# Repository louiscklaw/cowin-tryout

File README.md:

# COWIN_TRYOUT

DHT22  (Temperature and Humidity)
BMP280 (pressure sensor)
DS1307 (RTC)

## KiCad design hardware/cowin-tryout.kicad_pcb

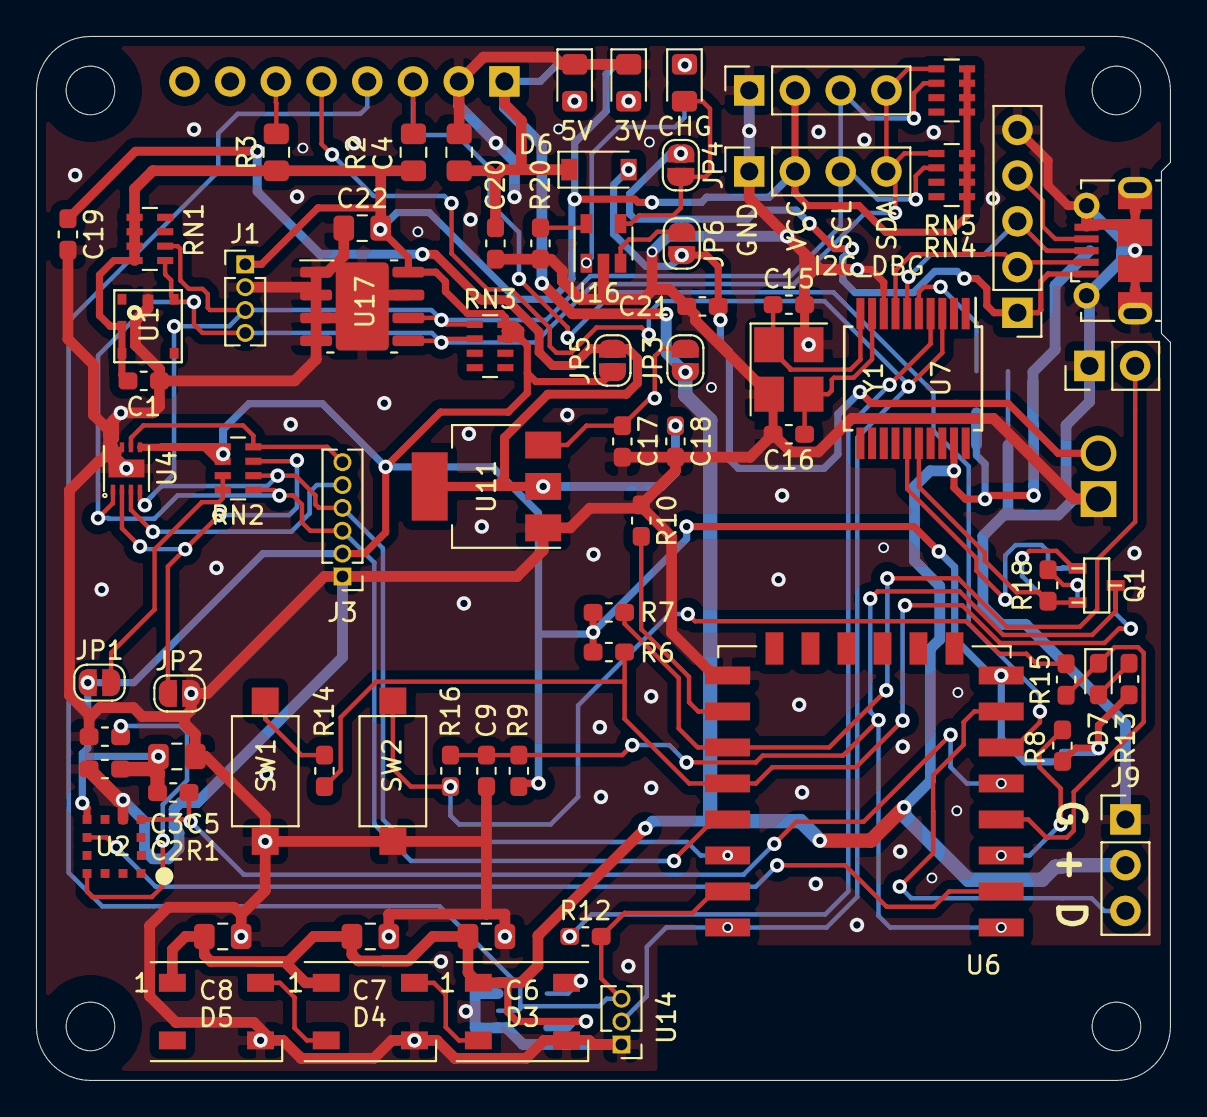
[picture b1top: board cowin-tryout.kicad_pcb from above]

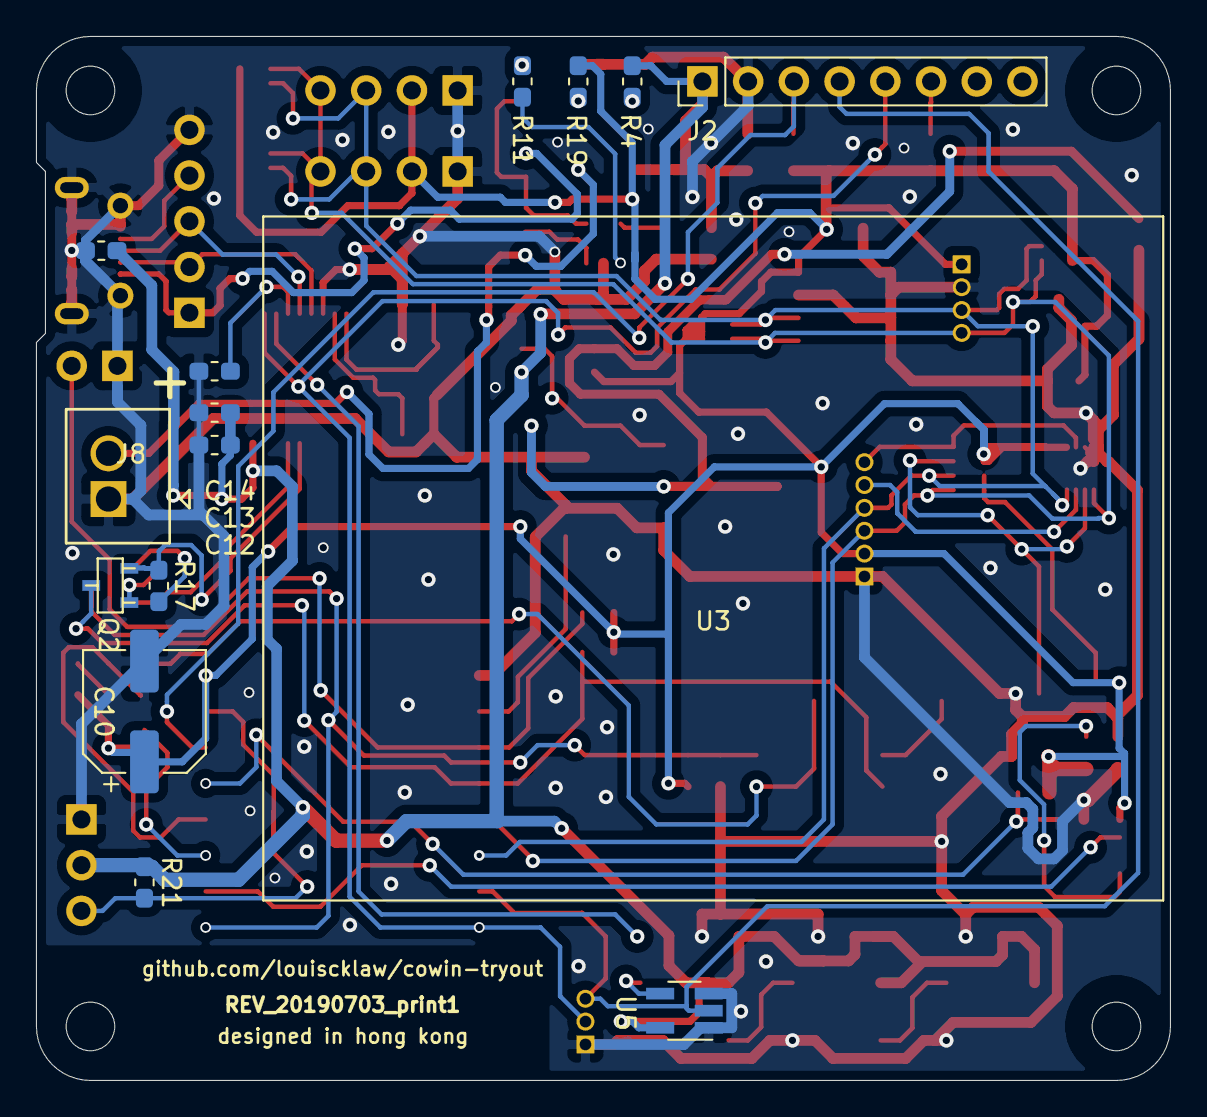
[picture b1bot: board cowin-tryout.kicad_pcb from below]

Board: 2 copper layers, 63.0 x 58.0 mm, 94 parts (15 on the bottom side), 51 nets.

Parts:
C1, C2, C9, C13, C17, C18: C104,0603; C_0603_1608Metric_Pad1.05x0.95mm_HandSolder
C3: C102,0603; C_0603_1608Metric_Pad1.05x0.95mm_HandSolder
C4: C106; C_0805_2012Metric_Pad1.15x1.40mm_HandSolder
C5: C104,0805; C_0805_2012Metric_Pad1.15x1.40mm_HandSolder
C6, C7, C8, C22: C106,0805; C_0805_2012Metric_Pad1.15x1.40mm_HandSolder
C10: CP100uf,10V; CP_Elec_6.3x5.3
C11: C475,0603; C_0603_1608Metric_Pad1.05x0.95mm_HandSolder
C12: C225,0603; C_0603_1608Metric_Pad1.05x0.95mm_HandSolder
C14: C103,0603; C_0603_1608Metric_Pad1.05x0.95mm_HandSolder
C15, C16: C22pf,0603; C_0603_1608Metric_Pad1.05x0.95mm_HandSolder
C19, C20, C21: C106,0603; C_0603_1608Metric_Pad1.05x0.95mm_HandSolder
D1: 5V; LED_0805_2012Metric_Pad1.15x1.40mm_HandSolder
D3, D4, D5: WS2812B; LED_WS2812B_5050_white
D6: D_1N4148_T4; D_SOD-123
D7: LED_BLUE,0603; LED_0603_1608Metric_Pad1.05x0.95mm_HandSolder
D8: 3V; LED_0805_2012Metric_Pad1.15x1.40mm_HandSolder
D9: CHG; LED_0805_2012Metric_Pad1.15x1.40mm_HandSolder
H1, H2, H3, H4: MOUNT_M2.5; MountingHole_2.7mm_M2.5,rpi_like
J1: BMP180_HEADER; PinHeader_1x04_P1.27mm_Vertical
J2: CONN_PMS; PinHeader_1x08_P2.54mm_Vertical
J3: SHT3x_HEADER; PinHeader_1x06_P1.27mm_Vertical
J7: DEBUG_HEADER; PinHeader_1x02_P2.54mm_Vertical
J8: BAT; JST_B2B-XH-A-2.54
J9: DHT22_HEADER; PinHeader_1x03_P2.54mm_Vertical
J10: USB_DBG; PinHeader_1x05_P2.54mm_Vertical
JP1: SolderJumper_2_Open_round; SolderJumper-2_P1.3mm_Open_RoundedPad1.0x1.5mm
JP2: J_ADDR; SolderJumper-2_P1.3mm_Open_RoundedPad1.0x1.5mm
JP3, JP4: 5V_EN; SolderJumper-2_P1.3mm_Open_RoundedPad1.0x1.5mm
JP5: 3V_EN; SolderJumper-2_P1.3mm_Open_RoundedPad1.0x1.5mm
JP6: OUT_EN; SolderJumper-2_P1.3mm_Open_RoundedPad1.0x1.5mm
Q1, Q2: SS9013_J3; 9013,J3,SOT23
R1, R20, R21: R103,0603; R_0603_1608Metric_Pad1.05x0.95mm_HandSolder
R2, R3: R103; R_0805_2012Metric_Pad1.15x1.40mm_HandSolder
R4: R102; R_0603_1608Metric_Pad1.05x0.95mm_HandSolder
R6, R7, R8, R9, R10, R17, R18: R123,0603; R_0603_1608Metric_Pad1.05x0.95mm_HandSolder
R11, R19: R102,0603; R_0603_1608Metric_Pad1.05x0.95mm_HandSolder
R12, R13, R14, R16: R471,0603; R_0603_1608Metric_Pad1.05x0.95mm_HandSolder
R15: R0,0603; R_0603_1608Metric_Pad1.05x0.95mm_HandSolder
RN1: RN_103,0603; R_Array_Concave_4x0603
RN2, RN3, RN4, RN5: RN_472,0603; R_Array_Concave_4x0603
SW1: FLASH_BUTTON; SW_SPST_CK_RS282G05A3
SW2: SW_RESET,2_leg,SMD; SW_SPST_CK_RS282G05A3
U1: BMP180
U2: ML8511
U3: PMS5003S_BODY
U4: SHT3x-DIS
U5: 74AHCT1G125; SOT-23-5_HandSoldering
U6: ESP12; ESP-12E
U7: CH340T; CH340T_SSOP-20
U8: USB_Micro; USB_Micro-B_Molex-105017-0001
U9: SSD1306-OLED-I2C; CONN_I2C_SSD1306
U10: I2C_DBG; CONN_I2C_SSD1306
U11: AMS1117-3.3; SOT-223-3_TabPin2
U12: DESIGNED_IN_HONG_KONG
U13: GITHUB_ADDRESS
U14: TTL_TERMINAL; PinHeader_1x03_P1.27mm_Vertical
U15: BOARD_REVISION
U16: MCP73831; MCP73831_SOT23_5
U17: 24C02_SOIC8; 24Cxx_SOIC8
Y1: O_12M,3225; OSC_3225

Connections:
+3V3: C1.2, C2.1, C5.2, C10.1, C22.2, J1.1, J3.2, JP1.1, JP5.1, R1.1, R2.1, R3.1, R6.2, R7.2, R8.2, R9.2, R13.1, R19.1, RN1.5, RN1.6, RN1.7, RN1.8, RN2.5, RN2.6, RN3.7, RN3.8, RN4.5, RN4.6, RN4.7, RN4.8, RN5.5, RN5.6, RN5.7, RN5.8, U1.2, U1.3, U2.7, U4.5, U6.8, U9.VCC, U10.VCC, U17.8
+5V: C4.1, C6.2, C7.2, C8.2, C11.2, C12.1, C13.1, C20.1, D3.1, D4.1, D5.1, D6.1, J2.1, J9.2, JP3.1, R4.1, R21.1, U5.5, U7.19
/DHT_OUT: J9.3, R21.2, U6.7
/GPIO12: J2.3, R2.2, U6.6
/RXD: J2.4, R12.2, U5.2, U6.21, U14.3
/SCL: J1.3, J3.4, RN1.2, RN2.2, RN3.1, RN4.2, RN5.2, U1.5, U4.4, U6.20, U9.SCL, U10.SCL, U17.6
/SDA: J1.4, J3.3, RN1.1, RN2.1, RN3.2, RN4.1, RN5.1, U1.6, U4.1, U6.19, U9.SDA, U10.SDA, U17.5
/SHT3X/ADDR: JP2.1, RN2.3, U4.2
/SHT3X/ALERT: J3.5, U4.3
/SHT3X/NRST: J3.6, RN2.4, U4.6
/TXD: J2.5, U6.22, U7.3, U14.2
/esp-12e/ADC: U2.8, U6.2
/esp-12e/EN: R8.1, U6.3
/esp-12e/GPIO0: Q2.3, R6.1, R14.1, U6.18
/esp-12e/GPIO2: J7.2, R7.1, U6.17
/esp-12e/GPIO15: R10.2, U6.16
/esp-12e/GPIO16: D7.1, R15.1, U6.4
/esp-12e/nRST: C9.1, Q1.3, R9.1, R16.1, U6.1
/esp-12e/usb_to_uart/DTR: Q2.2, R17.1, U7.15
/esp-12e/usb_to_uart/ID: J10.4, U8.4
/esp-12e/usb_to_uart/RTS: Q1.2, R18.1, U7.16
/esp-12e/usb_to_uart/RXD0: R12.1, U7.4
/esp-12e/usb_to_uart/USB_N: J10.2, U7.7, U8.2
/esp-12e/usb_to_uart/USB_P: J10.3, U7.6, U8.3
/pm2_5/SEN_RESET: J2.6, R3.2
/sunlight_uv/EN: R1.2, U2.4, U6.5
GND: C1.1, C2.2, C3.2, C4.2, C5.1, C6.1, C7.1, C8.1, C9.2, C10.2, C11.1, C12.2, C13.2, C14.2, C15.2, C16.2, C17.2, C18.2, C19.2, C20.2, C21.2, C22.1, D1.1, D3.3, D4.3, D5.3, D8.1, J1.2, J2.2, J3.1, J7.1, J8.1, J9.1, J10.5, JP2.2, R10.1, R20.1, SW1.2, SW2.2, U1.7, U2.5, U4.7, U4.8, U4.PAD, U5.1, U5.3, U6.15, U7.8, U8.5, U8.6, U8.7, U8.8, U8.9, U9.GND, U10.GND, U11.1, U14.1, U16.2, U17.1, U17.2, U17.3, U17.4, U17.7, Y1.2
unnamed: C3.1, U2.10
unnamed: C14.1, U7.5
unnamed: C15.1, U7.10, Y1.1
unnamed: C16.1, U7.9, Y1.3
unnamed: C17.1, JP3.2, U11.3
unnamed: C18.1, C19.1, JP5.2, U11.2
unnamed: D1.2, R4.2
unnamed: D3.2, D4.4
unnamed: D3.4, U5.4
unnamed: D4.2, D5.4
unnamed: D7.2, R13.2
unnamed: D8.2, R19.2
unnamed: D9.1, R11.2
unnamed: D9.2, JP4.2, U16.4
unnamed: JP1.2, RN2.7, RN2.8
unnamed: JP6.1, U16.3
unnamed: Q1.1, R17.2
unnamed: Q2.1, R18.2
unnamed: R11.1, U16.1
unnamed: R14.2, SW1.1
unnamed: R15.2, R16.2, SW2.1
unnamed: R20.2, U16.5
VBUS: J10.1, JP4.1, U8.1
Vbat: C21.1, D6.2, J8.2, JP6.2

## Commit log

2019-06-26 update,
2019-07-04 remove bak files,
2020-05-05 ci: init travis token,
2020-05-05 ci: init travis build config,
